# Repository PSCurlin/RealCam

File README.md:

# RealCam

RealCam is a remote viewing device who's orientation can be controlled by the user's head position.

## Servos and IMU

Currently, these are the only items utilizing the MSP432 and are written in C.

## Camera

The camera interfaces with an Arduino UNO and uses Arduino code.

## USB-SPI interface

This interface is currently being tested by sending values through a terminal provided by MikroElektronica. The SPI protocol is tested with an Arduino which behaves as a slave.

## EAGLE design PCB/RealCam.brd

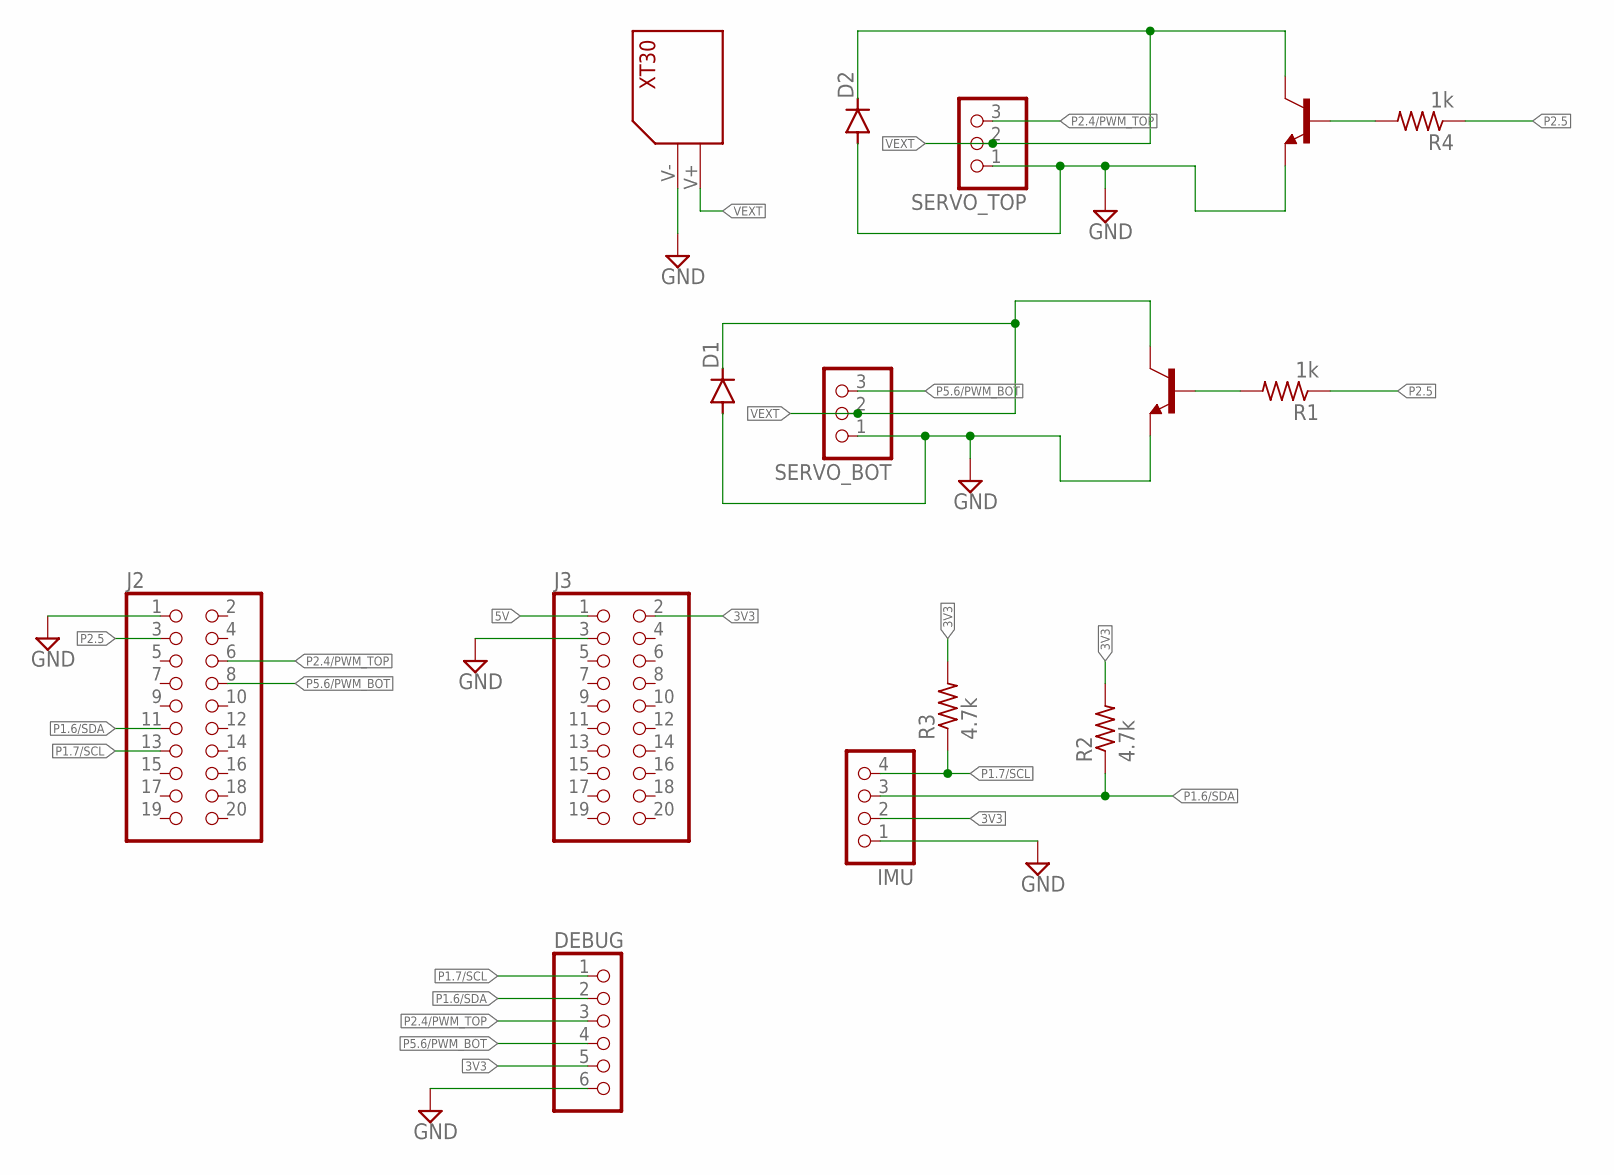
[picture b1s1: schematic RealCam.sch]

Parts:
D1, D2: 1N4933; DO41-10
DEBUG: PINHD-1X6; 1X06
IMU: PINHD-1X4; 1X04
J2, J3: PINHD-2X10; 2X10
NPN_BC1, NPN_BC337: 2N3565; TO92
R1, R4: 1k; R0805
R2, R3: 4.7k; R0805
SERVO_BOT: PINHD-1X3; 1X03
SERVO_TOP: PINHD-1X3; 1X03
U$1: XT30_RIGHT_ANGLE

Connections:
3V3: DEBUG.5, IMU.2, J3.2, R2.2, R3.2
5V: J3.1
GND: D1.A, D2.A, DEBUG.6, IMU.1, J2.1, J3.3, NPN_BC1.3 (E), NPN_BC337.3 (E), SERVO_BOT.1, SERVO_TOP.1, U$1.V-
unnamed: NPN_BC337.2 (B), R1.2
unnamed: NPN_BC1.2 (B), R4.2
P1.6/SDA: DEBUG.2, IMU.3, J2.11, R2.1
P1.7/SCL: DEBUG.1, IMU.4, J2.13, R3.1
P2.4/PWM_TOP: DEBUG.3, J2.6, SERVO_TOP.3
P2.5: J2.3, R1.1, R4.1
P5.6/PWM_BOT: DEBUG.4, J2.8, SERVO_BOT.3
VEXT: D1.C, D2.C, NPN_BC1.1 (C), NPN_BC337.1 (C), SERVO_BOT.2, SERVO_TOP.2, U$1.V+

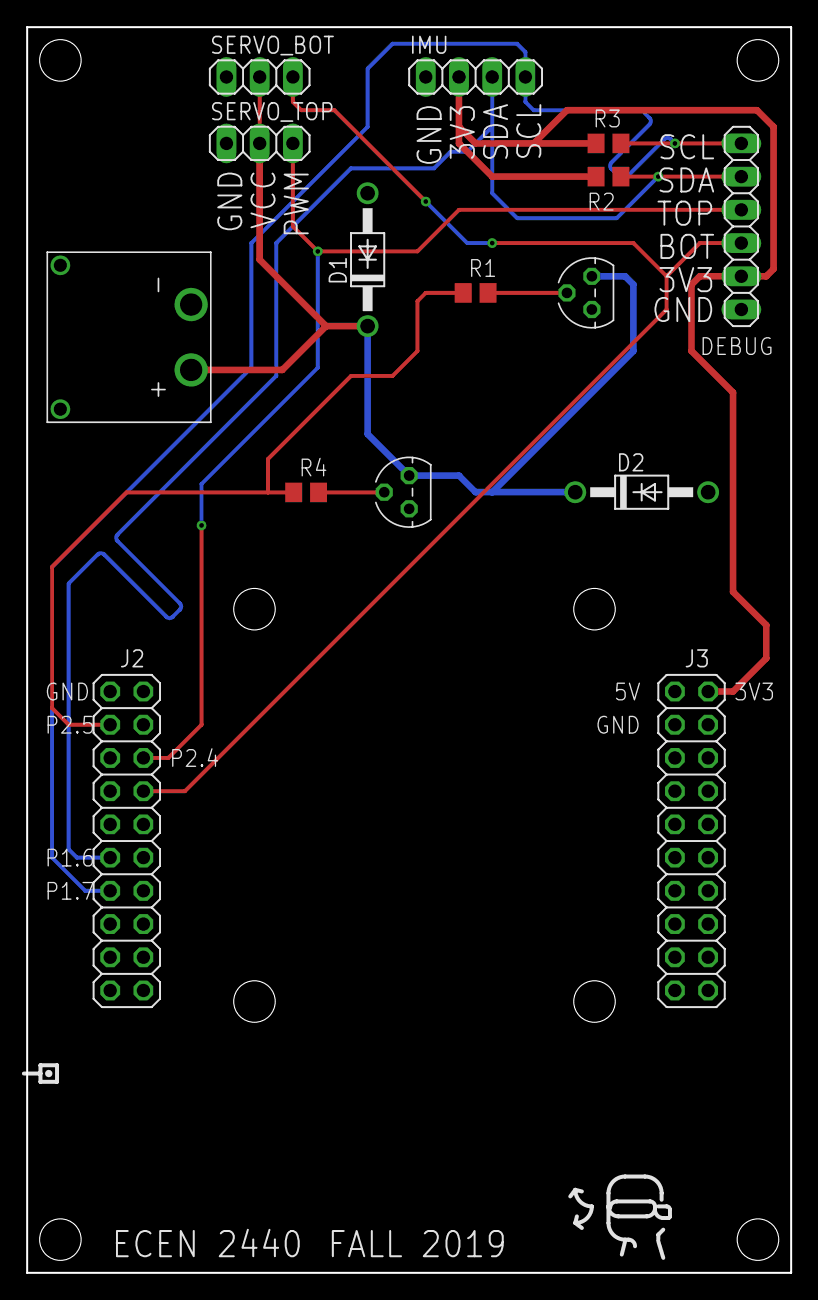
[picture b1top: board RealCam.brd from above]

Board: 2 copper layers, 58.4 x 95.2 mm, 23 parts (0 on the bottom side), 10 nets.

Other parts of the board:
U$2, U$3, U$4, U$5, U$6, U$7, U$8, U$9: MOUNTHOLE_125MIL

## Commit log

2019-11-04 Add files via upload
    just making some files
2019-11-06 added PMW files & some technical references
2019-11-11 blah
2019-11-11 wrong folders were uploaded previously
2019-11-22 organisation and some pics
2019-11-22 stuff
2019-12-08 pwm final
2019-12-08 pwm update h
2019-12-08 integration of servos and imu
2019-12-08 added documentation and PCB
2019-12-11 updating pwm.c with comments (not done)
2019-12-11 updating pwm.h with comments (not done)
2019-12-11 updating some comments on main.c
2019-12-11 updating more pwm.c comments
2019-12-11 updating pwm.h comments more
2019-12-11 updating main.c with stuff I changed in pwm.c
2019-12-11 took out unnecessary stuff in i2c.c
2019-12-11 commenting
2019-12-11 comments done for ICM file
2019-12-11 commented AK09916
2019-12-11 pwm comments
